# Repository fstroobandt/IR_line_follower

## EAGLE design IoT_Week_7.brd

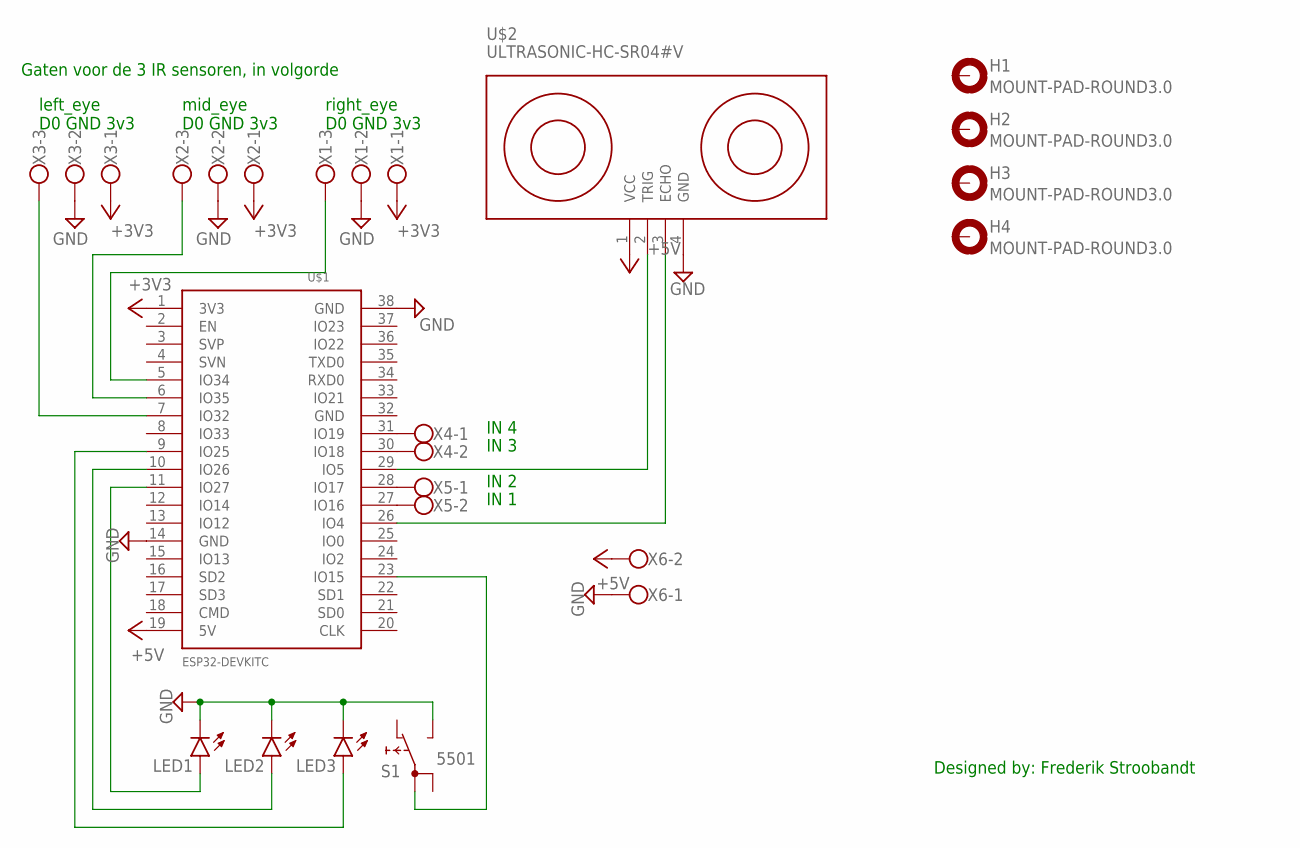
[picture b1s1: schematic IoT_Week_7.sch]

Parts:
H1, H2, H3, H4: MOUNT-PAD-ROUND3.0; 3,0-PAD
LED1, LED2, LED3: LAP4-BOTTOM; P47F-BOTTOM
S1: 5501
U$1: ESP32DEVKITC; ESP32-DEVKITC
U$2: ULTRASONIC-HC-SR04#V
X1, X2, X3: W237-103
X4, X5, X6: W237-102

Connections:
+3V3: U$1.1 (3V3), X1.1, X2.1, X3.1
+5V: U$1.19 (5V), U$2.1 (VCC), X6.2
GND: LED1.C, LED2.C, LED3.C, S1.NO, U$1.14 (GND), U$1.38 (GND), U$2.4 (GND), X1.2, X2.2, X3.2, X6.1
unnamed: U$1.27 (IO16), X5.2
unnamed: U$1.28 (IO17), X5.1
unnamed: U$1.31 (IO19), X4.1
unnamed: U$1.30 (IO18), X4.2
unnamed: U$1.5 (IO34), X1.3
unnamed: U$1.6 (IO35), X2.3
unnamed: U$1.7 (IO32), X3.3
unnamed: LED3.A, U$1.9 (IO25)
unnamed: LED2.A, U$1.10 (IO26)
unnamed: LED1.A, U$1.11 (IO27)
unnamed: U$1.29 (IO5), U$2.2 (TRIG)
unnamed: S1.1A, U$1.23 (IO15)
unnamed: U$1.26 (IO4), U$2.3 (ECHO)

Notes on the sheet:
Gaten voor de 3 IR sensoren, in volgorde
left_eye D0 GND 3v3
mid_eye D0 GND 3v3
right_eye D0 GND 3v3
IN 4
IN 3
IN 2
IN 1
Designed by: Frederik Stroobandt

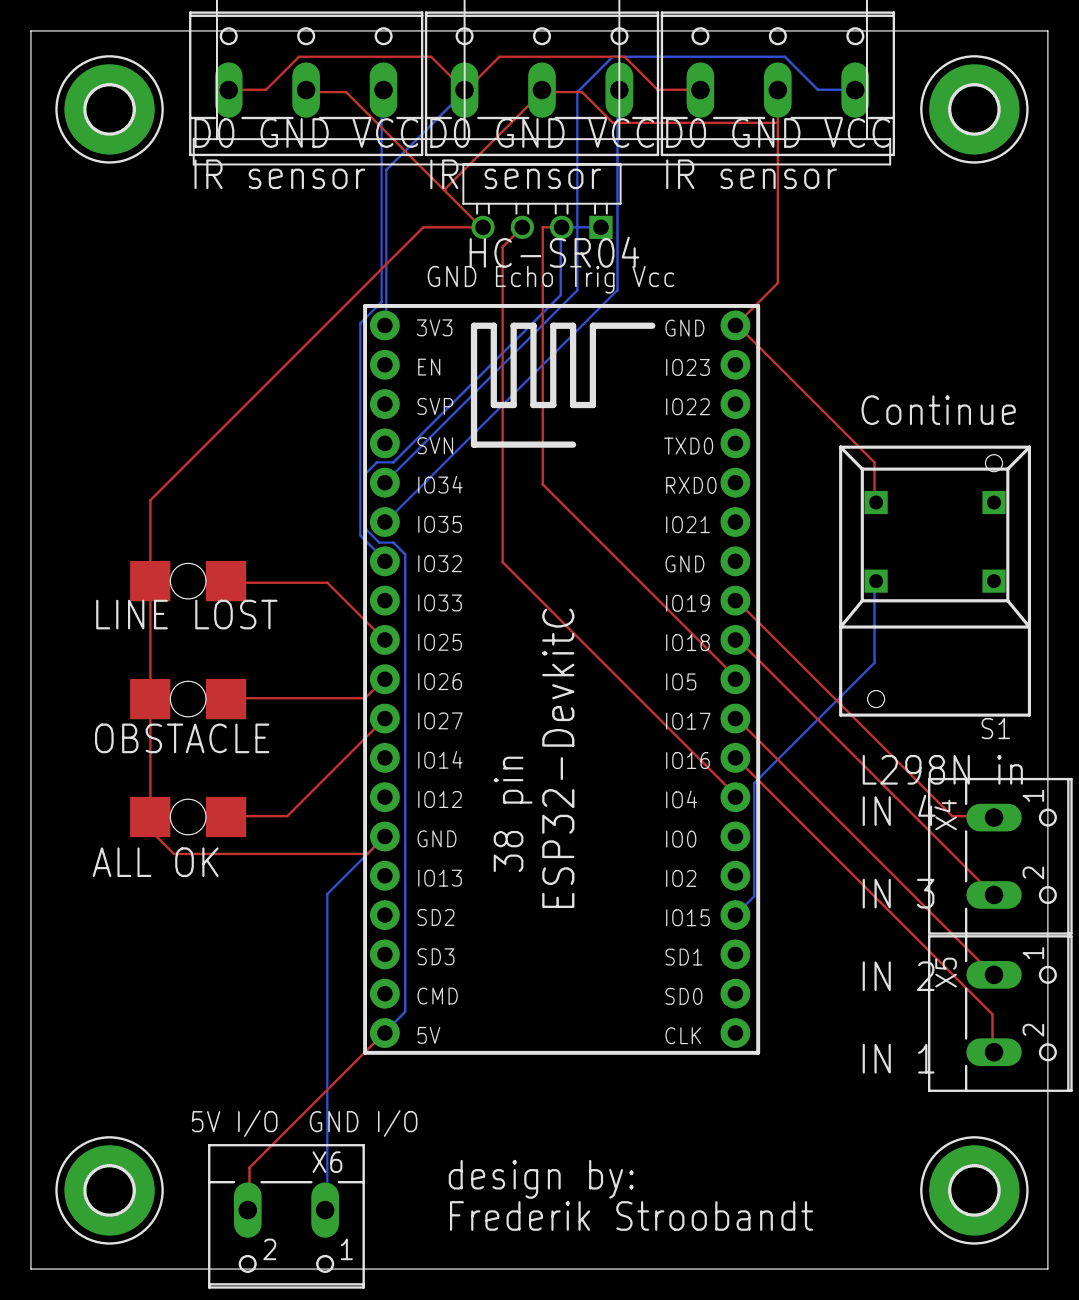
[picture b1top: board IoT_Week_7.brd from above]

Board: 2 copper layers, 65.7 x 80.0 mm, 16 parts (0 on the bottom side), 16 nets.

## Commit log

2021-05-31 bestanden geüpdate omdat de links niet werkte in de pdf

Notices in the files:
parts and their libraries:
diy-modules: Released under the Creative Commons Attribution 4.0 International License: http://creativecommons.org/licenses/by/4.0
